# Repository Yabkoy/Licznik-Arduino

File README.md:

# **Arduino Counter**

I created a school lesson counter that calculate time to next break and the next lesson. I used Arduino to develop it, but after that I took a ATMega chip and created a separate board for that in kicad with schematics and when I insert programmed the chip and other electronic parts everything should work properly.

## **Electronic Parts**
- ATMega328
- Led diode 
- crystal  16 MHz
- Resistor 10K
- Ceramic capacitor 22pF
- Max 7219 7 segment
- RTC Module

## **KICAD**

Beside the source code for Arduino the repository contains the KiCad Project with full schematic and PCB for this counter.
So in the KicadProj/Licznik directory you will find all files that you will need.

**[KiCad Download](https://www.kicad.org/)**

### **Dependencies**
As a dependencies I used two libraries for DS3231 chip and Max7219 chip. The source code of libs is containing in libraries folder. 
**NOTE: THE CODE OF THIS LIBRARIES IS NOT MINE**

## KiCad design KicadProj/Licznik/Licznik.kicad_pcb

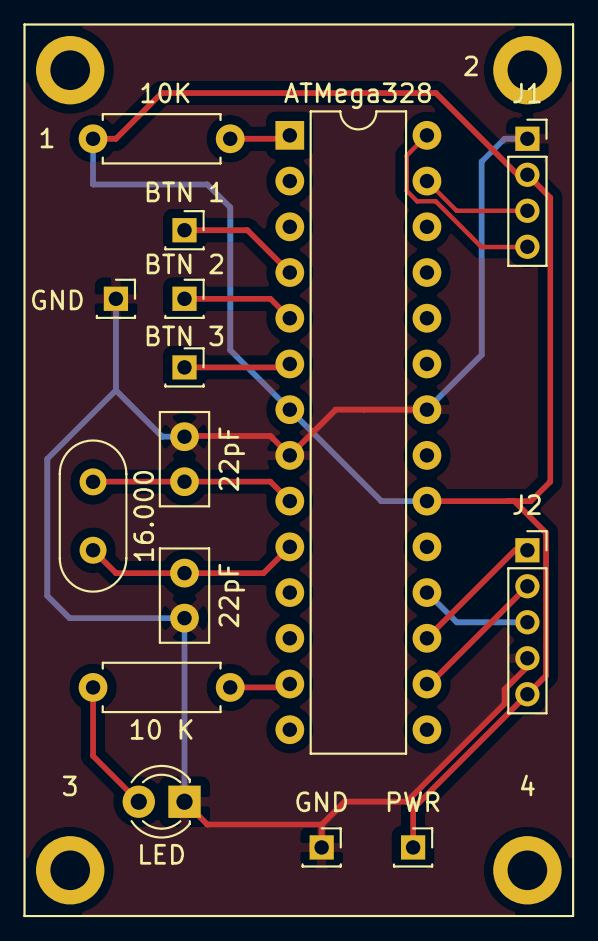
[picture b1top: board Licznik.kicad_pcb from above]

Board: 2 copper layers, 19 parts (0 on the bottom side), 15 nets.

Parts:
1, 2, 3, 4: 1; MountingHole_2.2mm_M2_DIN965_Pad
10 K, 10K: R; R_Axial_DIN0207_L6.3mm_D2.5mm_P7.62mm_Horizontal
16.000: Crystal; Crystal_HC52-6mm_Vertical
22pF, 22pF#2: C; C_Disc_D5.0mm_W2.5mm_P2.50mm
ATMega328: ATmega328P-PU; DIP-28_W7.62mm
BTN 1, BTN 2, BTN 3: +; PinSocket_1x01_P2.00mm_Vertical
GND: -; PinSocket_1x01_P2.00mm_Vertical
GND#2: GND_IN; PinSocket_1x01_P2.00mm_Vertical
J1: rtc; PinSocket_1x04_P2.00mm_Vertical
J2: 7seg; PinSocket_1x05_P2.00mm_Vertical
LED: LED; LED_D3.0mm
PWR: POWER_IN; PinSocket_1x01_P2.00mm_Vertical

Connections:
+5V: 10K.2, ATMega328.7, ATMega328.20, J1.2, J2.5, PWR.1
GND: 22pF.1, 22pF#2.2, ATMega328.8, ATMega328.22, GND.1, GND#2.1, J1.1, J2.4, LED.1
unnamed: 16.000.2, 22pF#2.1, ATMega328.10
unnamed: 16.000.1, 22pF.2, ATMega328.9
unnamed: 10 K.2, LED.2
unnamed: ATMega328.27, J1.3
unnamed: ATMega328.28, J1.4
unnamed: ATMega328.17, J2.1
unnamed: ATMega328.16, J2.2
unnamed: ATMega328.18, J2.3
unnamed: ATMega328.6, BTN 3.1
unnamed: ATMega328.5, BTN 2.1
unnamed: ATMega328.4, BTN 1.1
unnamed: 10K.1, ATMega328.1
unnamed: 10 K.1, ATMega328.13

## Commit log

2021-05-15 multiply to files
2021-05-15 Change name of clock testing to every test of this project and organization
2021-05-15 add libs.h file for organization and bug fixes
2021-05-15 Couter System working
2021-05-15 Code Cleaning
2021-05-15 Led on select Button
2021-05-16 Add 7-seg display working
2021-05-16 Fix dot in display function
2021-05-16 Add more characters to display library and add zero setting function
2021-05-16 Add libs and oldSystemCout file
2021-05-17 Code optimization and cleaning
2021-05-20 Add Kicad Project and basic schematic added
2021-05-20 created PCB board
2021-05-20 Add gitignore file
2022-03-22 update schematics
2022-03-22 update gitignore and added README.md file with images
2022-03-22 fixed README Images and fix other markdown things
2022-03-22 fix pcb issue with markdown
2022-03-22 add libraries folder
